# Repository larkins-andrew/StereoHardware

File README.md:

# StereoBoy Hardware
# KiCad hardware files for Original GameBoy Color cartridge, GameBoy Pocket logic board, and StereoBoy logic board

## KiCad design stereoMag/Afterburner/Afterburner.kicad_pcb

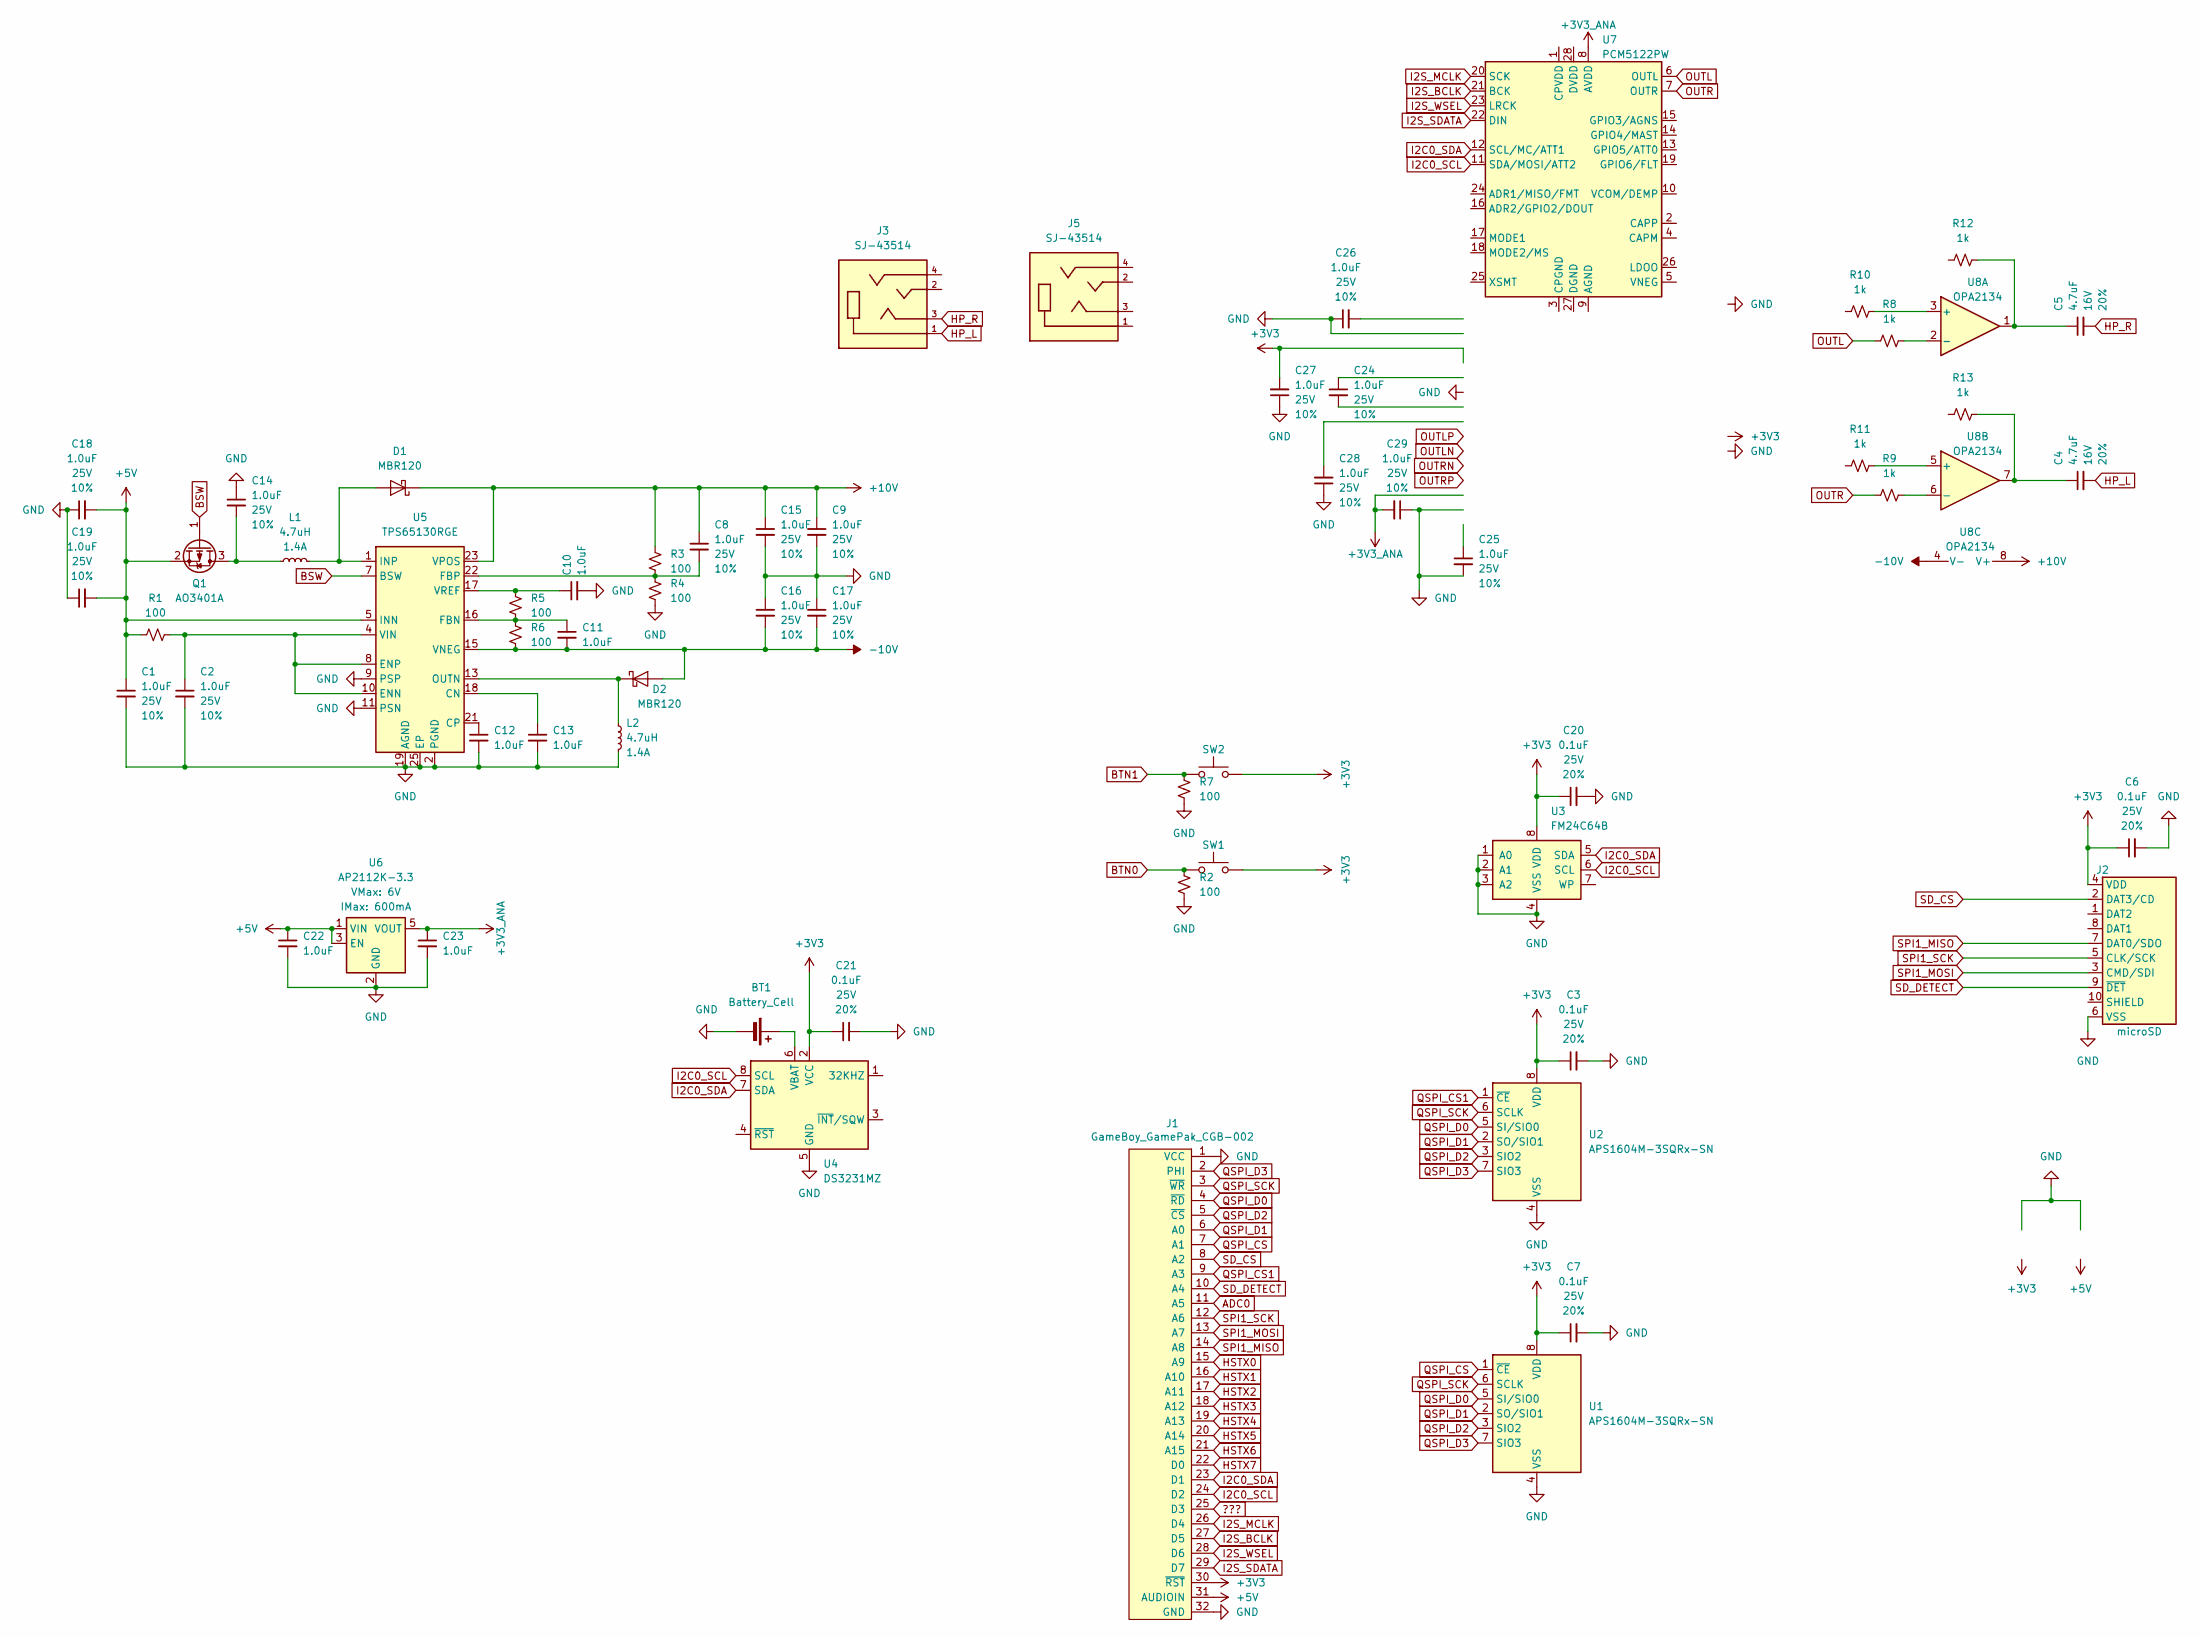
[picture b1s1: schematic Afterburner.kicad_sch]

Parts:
BT1: Battery_Cell; BatteryHolder_Keystone_3001_1x12mm
C1, C2, C10, C12, C13, C22, C23: 1.0uF; C_0603_1608Metric; Voltage 25V; Tolerance 10%
C3, C7, C20, C21: 0.1uF; C_0805_2012Metric; Voltage 25V; Tolerance 20%
C4, C5: 4.7uF; C_1206_3216Metric; Voltage 16V; Tolerance 20%
C6: 0.1uF; C_0603_1608Metric; Voltage 25V; Tolerance 20%
C8, C9, C11, C15, C16, C17, C18, C19: 1.0uF; C_1206_3216Metric; Voltage 25V; Tolerance 10%
C14, C28: 1.0uF; C_0805_2012Metric; Voltage 25V; Tolerance 10%
C24, C25, C26, C27, C29: 1.0uF; C_0402_1005Metric; Voltage 25V; Tolerance 10%
D1, D2: MBR120; D_SOD-123F
J1: GameBoy_GamePak_CGB-002; GameBoy_GamePak_CGB-002_P1.50mm_Edge
J2: microSD; microSD_External_Pin
J3, J5: SJ-43514; SJ_43514; PART_REV 1.04
L1, L2: 4.7uH; L_APV_ANR4012
Q1: AO3401A; SOT-23
R1, R2, R3, R4, R5, R6, R7: 100; R_0603_1608Metric
R8, R9, R10, R11, R12, R13: 1k; R_0603_1608Metric
SW1, SW2: PTH_RA_7.4x4.3mm; Push_PTH_RA_7.4x4.3mm
U1, U2: APS1604M-3SQRx-SN; SOIC-8_3.9x4.9mm_P1.27mm
U3: FM24C64B; SOIC-8_3.9x4.9mm_P1.27mm
U4: DS3231MZ; SOIC-8_3.9x4.9mm_P1.27mm
U5: TPS65130RGE; VQFN-24-1EP_4x4mm_P0.5mm_EP2.45x2.45mm_ThermalVias
U6: AP2112K-3.3; SOT23-5
U7: PCM5122PW; TSSOP-28_4.4x9.7mm_P0.65mm
U8: OPA2134

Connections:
+3V3: C3.1, C6.1, C7.1, C20.1, C21.1, C27.2, J1.30 (~RST), J2.4 (VDD), SW1.2, SW2.2, U1.8 (VDD), U2.8 (VDD), U3.8 (VDD), U4.2 (VCC)
+3V3_ANA: C23.1, C29.2, U6.5 (VOUT), U7.8 (AVDD)
+5V: C1.1, C18.2, C19.2, C22.1, J1.31 (AUDIOIN), Q1.2 (S), R1.1, U5.5 (INN), U5.6 (INN), U6.1 (VIN), U6.3 (EN)
+10V: C8.1, C9.1, C15.1, D1.1 (K), R3.2, U5.23 (VPOS), U8.8 (V+)
-10V: C11.2, C16.2, C17.2, D2.2 (A), R6.1, U5.15 (VNEG), U8.4 (V-)
???: J1.25 (D3)
ADC0: J1.11 (A5)
BSW: Q1.1 (G), U5.7 (BSW)
BTN0: R2.2, SW1.1
BTN1: R7.2, SW2.1
GND: BT1.2 (-), C1.2, C2.2, C3.2, C6.2, C7.2, C9.2, C10.2, C12.2, C13.2, C14.1, C15.2, C16.1, C17.1, C18.1, C19.1, C20.2, C21.2, C22.2, C23.2, C25.2, C26.1, C27.1, C28.1, C29.1, J1.1 (VCC), J1.32 (GND), J2.6 (VSS), L2.2, R2.1, R4.1, R7.1, U1.4 (VSS), U2.4 (VSS), U3.1 (A0), U3.2 (A1), U3.3 (A2), U3.4 (VSS), U4.5 (GND), U5.2 (PGND), U5.3 (PGND), U5.9 (PSP), U5.11 (PSN), U5.19 (AGND), U5.25 (EP), U6.2 (GND)
HP_L: C4.2, J3.1
HP_R: C5.2, J3.3
HSTX0: J1.15 (A9)
HSTX1: J1.16 (A10)
HSTX2: J1.17 (A11)
HSTX3: J1.18 (A12)
HSTX4: J1.19 (A13)
HSTX5: J1.20 (A14)
HSTX6: J1.21 (A15)
HSTX7: J1.22 (D0)
I2C0_SCL: J1.24 (D2), U3.6 (SCL), U4.8 (SCL), U7.11 (SDA/MOSI/ATT2)
I2C0_SDA: J1.23 (D1), U3.5 (SDA), U4.7 (SDA), U7.12 (SCL/MC/ATT1)
I2S_BCLK: J1.27 (D5), U7.21 (BCK)
I2S_MCLK: J1.26 (D4), U7.20 (SCK)
I2S_SDATA: J1.29 (D7), U7.22 (DIN)
I2S_WSEL: J1.28 (D6), U7.23 (LRCK)
unnamed: BT1.1 (+), U4.6 (VBAT)
unnamed: C4.1, R13.2, U8.7
unnamed: C5.1, R12.2, U8.1
unnamed: D1.2 (A), L1.2, U5.1 (INP), U5.24 (INP)
unnamed: D2.1 (K), L2.1, U5.13 (OUTN), U5.14 (OUTN)
unnamed: C14.2, L1.1, Q1.3 (D)
unnamed: C13.1, U5.18 (CN)
unnamed: C12.1, U5.21 (CP)
unnamed: C2.1, R1.2, U5.4 (VIN), U5.8 (ENP), U5.10 (ENN)
unnamed: C11.1, R5.1, R6.2, U5.16 (FBN)
unnamed: C8.2, R3.1, R4.2, U5.22 (FBP)
unnamed: C10.1, R5.2, U5.17 (VREF)
unnamed: R10.2, U8.3 (+)
unnamed: R8.2, U8.2 (-)
unnamed: R11.2, U8.5 (+)
unnamed: R9.2, U8.6 (-)
OUTL: R8.1, U7.6 (OUTL)
OUTR: R9.1, U7.7 (OUTR)
QSPI_CS: J1.7 (A1), U1.1 (~CE)
QSPI_CS1: J1.9 (A3), U2.1 (~CE)
QSPI_D0: J1.4 (~RD), U1.5 (SI/SIO0), U2.5 (SI/SIO0)
QSPI_D1: J1.6 (A0), U1.2 (SO/SIO1), U2.2 (SO/SIO1)
QSPI_D2: J1.5 (~CS), U1.3 (SIO2), U2.3 (SIO2)
QSPI_D3: J1.2 (PHI), U1.7 (SIO3), U2.7 (SIO3)
QSPI_SCK: J1.3 (~WR), U1.6 (SCLK), U2.6 (SCLK)
SD_CS: J1.8 (A2), J2.2 (DAT3/CD)
SD_DETECT: J1.10 (A4), J2.9 (~DET)
SPI1_MISO: J1.14 (A8), J2.7 (DAT0/SDO)
SPI1_MOSI: J1.13 (A7), J2.3 (CMD/SDI)
SPI1_SCK: J1.12 (A6), J2.5 (CLK/SCK)

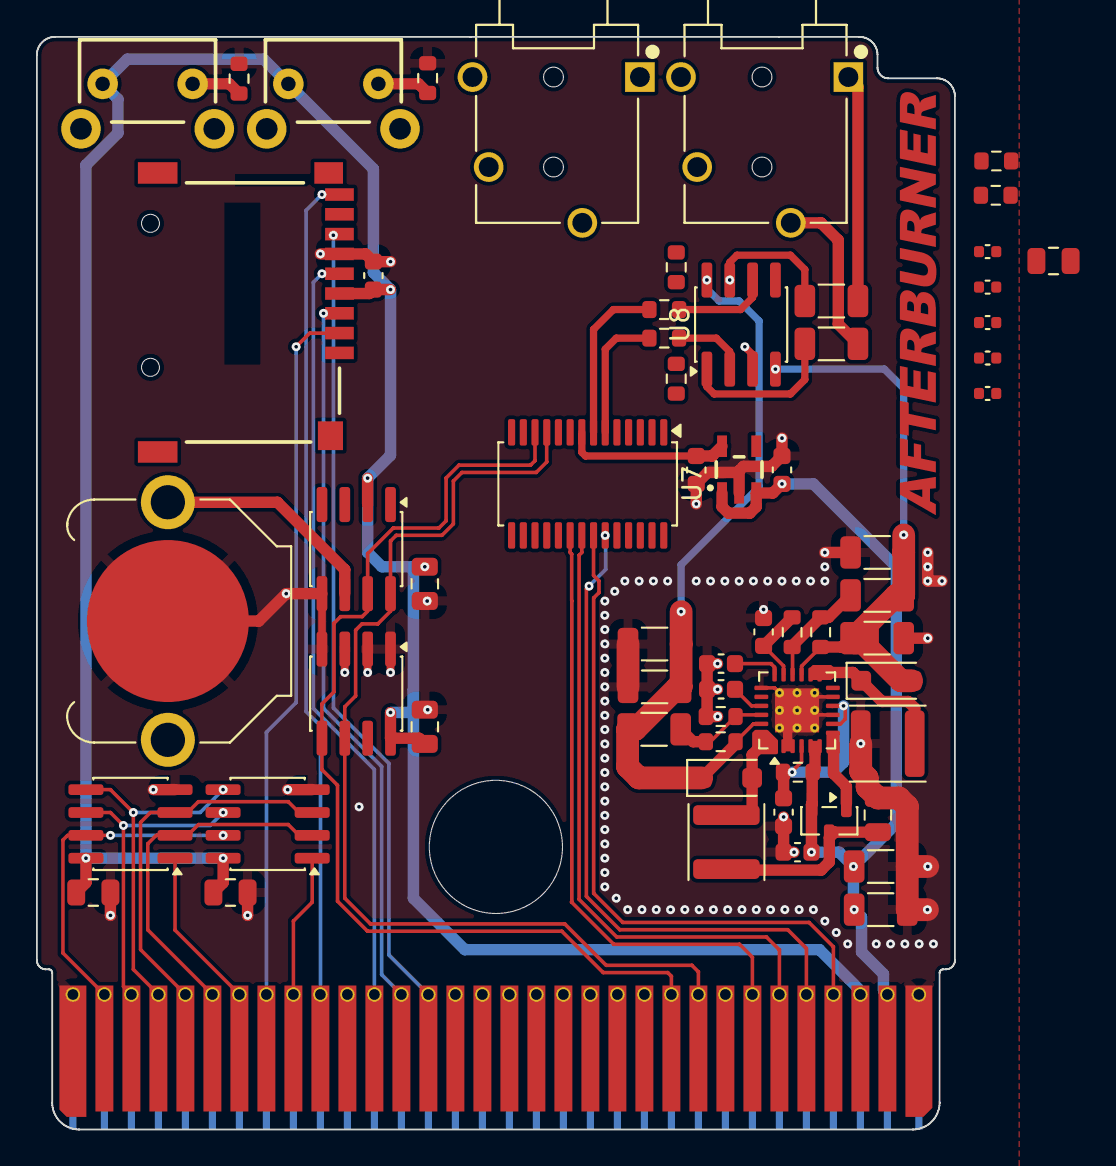
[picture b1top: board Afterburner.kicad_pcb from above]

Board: 2 copper layers, 51.0 x 60.7 mm, 62 parts (0 on the bottom side), 47 nets.

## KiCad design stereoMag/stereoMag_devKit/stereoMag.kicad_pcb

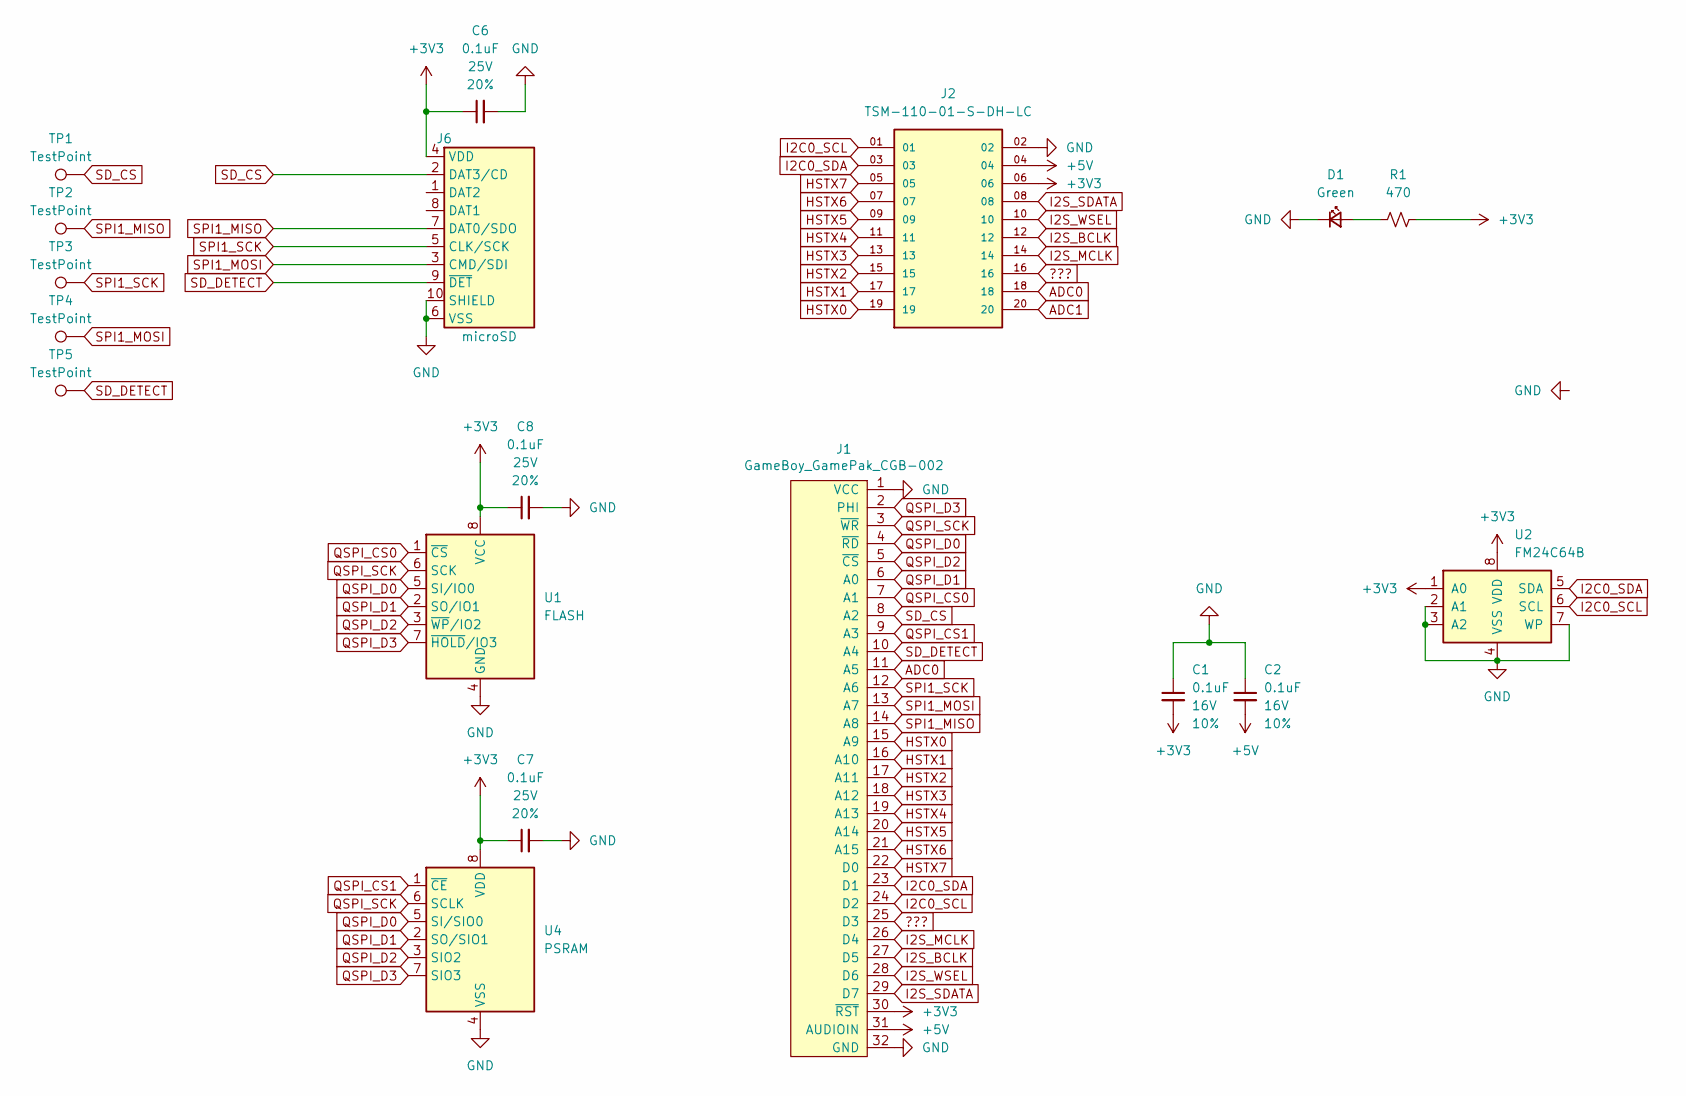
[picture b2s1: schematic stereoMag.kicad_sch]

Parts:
C1, C2: 0.1uF; C_1206_3216Metric; Voltage 16V; Tolerance 10%
C6, C7, C8: 0.1uF; C_0603_1608Metric; Voltage 25V; Tolerance 20%
D1: Green; LED_0603_1608Metric_Green
J1: GameBoy_GamePak_CGB-002; GameBoy_GamePak_CGB-002_P1.50mm_Edge
J2: TSM-110-01-S-DH-LC; SAMTEC_TSM-110-01-S-DH-LC; PARTREV R
J6: microSD; microSD_External_Pin
R1: 470; R_0603_1608Metric
TP1, TP2, TP3, TP4, TP5: TestPoint; TestPoint_Pad_D1.0mm
U1: FLASH; SOIC-8_3.9x4.9mm_P1.27mm
U2: FM24C64B; SOIC-8_3.9x4.9mm_P1.27mm
U4: PSRAM; SOIC-8_3.9x4.9mm_P1.27mm

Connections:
+3V3: C1.2, C6.1, C7.1, C8.1, J1.30 (~RST), J2.06, J6.4 (VDD), R1.2, U1.8 (VCC), U2.1 (A0), U2.8 (VDD), U4.8 (VDD)
+5V: C2.2, J1.31 (AUDIOIN), J2.04
???: J1.25 (D3), J2.16
ADC0: J1.11 (A5), J2.18
ADC1: J2.20
GND: C1.1, C2.1, C6.2, C7.2, C8.2, D1.1 (K), J1.1 (VCC), J1.32 (GND), J2.02, J6.6 (VSS), J6.10 (SHIELD), U1.4 (GND), U2.2 (A1), U2.3 (A2), U2.4 (VSS), U2.7 (WP), U4.4 (VSS)
HSTX0: J1.15 (A9), J2.19
HSTX1: J1.16 (A10), J2.17
HSTX2: J1.17 (A11), J2.15
HSTX3: J1.18 (A12), J2.13
HSTX4: J1.19 (A13), J2.11
HSTX5: J1.20 (A14), J2.09
HSTX6: J1.21 (A15), J2.07
HSTX7: J1.22 (D0), J2.05
I2C0_SCL: J1.24 (D2), J2.01, U2.6 (SCL)
I2C0_SDA: J1.23 (D1), J2.03, U2.5 (SDA)
I2S_BCLK: J1.27 (D5), J2.12
I2S_MCLK: J1.26 (D4), J2.14
I2S_SDATA: J1.29 (D7), J2.08
I2S_WSEL: J1.28 (D6), J2.10
unnamed: D1.2 (A), R1.1
QSPI_CS0: J1.7 (A1), U1.1 (~CS)
QSPI_CS1: J1.9 (A3), U4.1 (~CE)
QSPI_D0: J1.4 (~RD), U1.5 (SI/IO0), U4.5 (SI/SIO0)
QSPI_D1: J1.6 (A0), U1.2 (SO/IO1), U4.2 (SO/SIO1)
QSPI_D2: J1.5 (~CS), U1.3 (~WP/IO2), U4.3 (SIO2)
QSPI_D3: J1.2 (PHI), U1.7 (~HOLD/IO3), U4.7 (SIO3)
QSPI_SCK: J1.3 (~WR), U1.6 (SCK), U4.6 (SCLK)
SD_CS: J1.8 (A2), J6.2 (DAT3/CD), TP1.1
SD_DETECT: J1.10 (A4), J6.9 (~DET), TP5.1
SPI1_MISO: J1.14 (A8), J6.7 (DAT0/SDO), TP2.1
SPI1_MOSI: J1.13 (A7), J6.3 (CMD/SDI), TP4.1
SPI1_SCK: J1.12 (A6), J6.5 (CLK/SCK), TP3.1

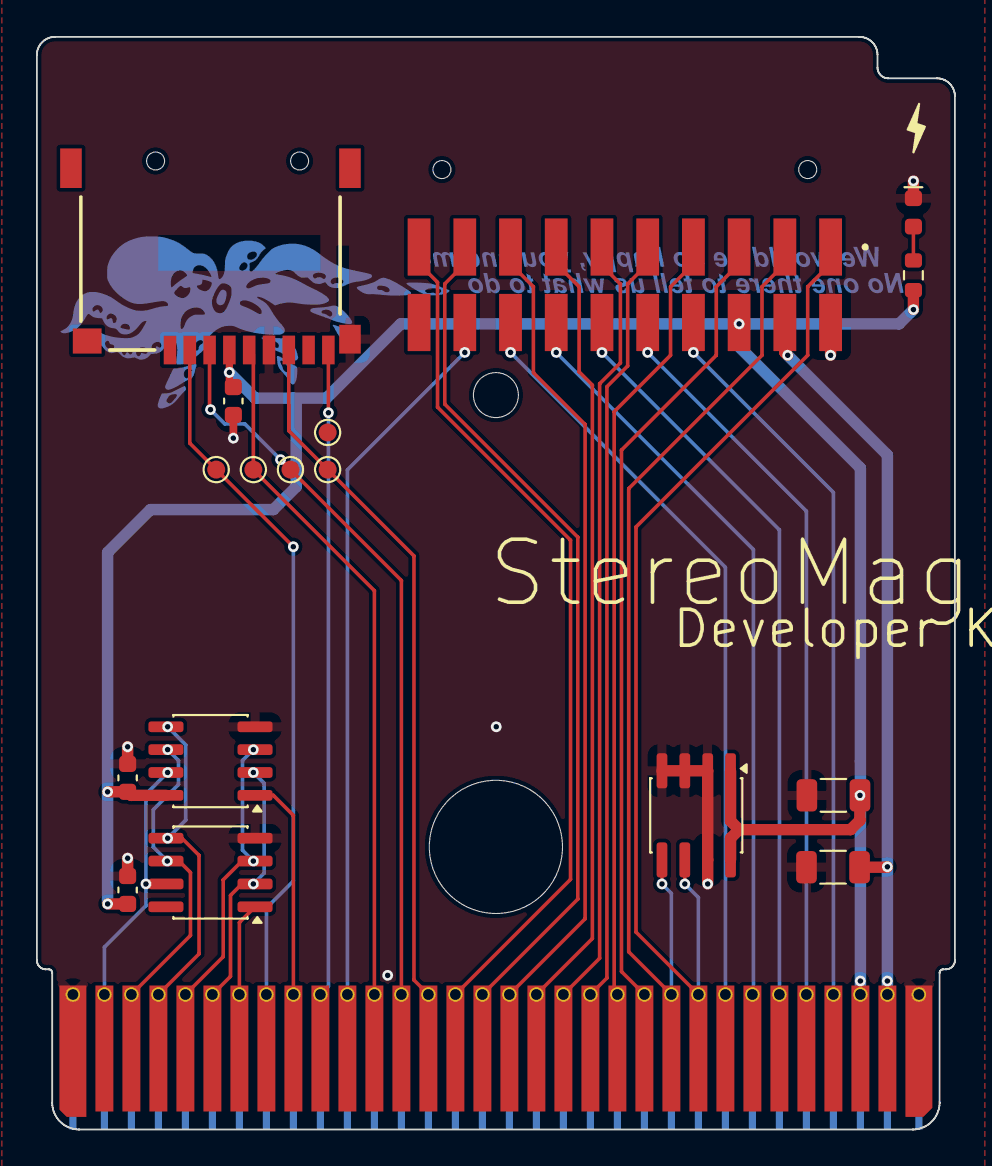
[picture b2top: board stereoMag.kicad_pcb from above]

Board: 2 copper layers, 51.0 x 60.7 mm, 18 parts (0 on the bottom side), 32 nets.

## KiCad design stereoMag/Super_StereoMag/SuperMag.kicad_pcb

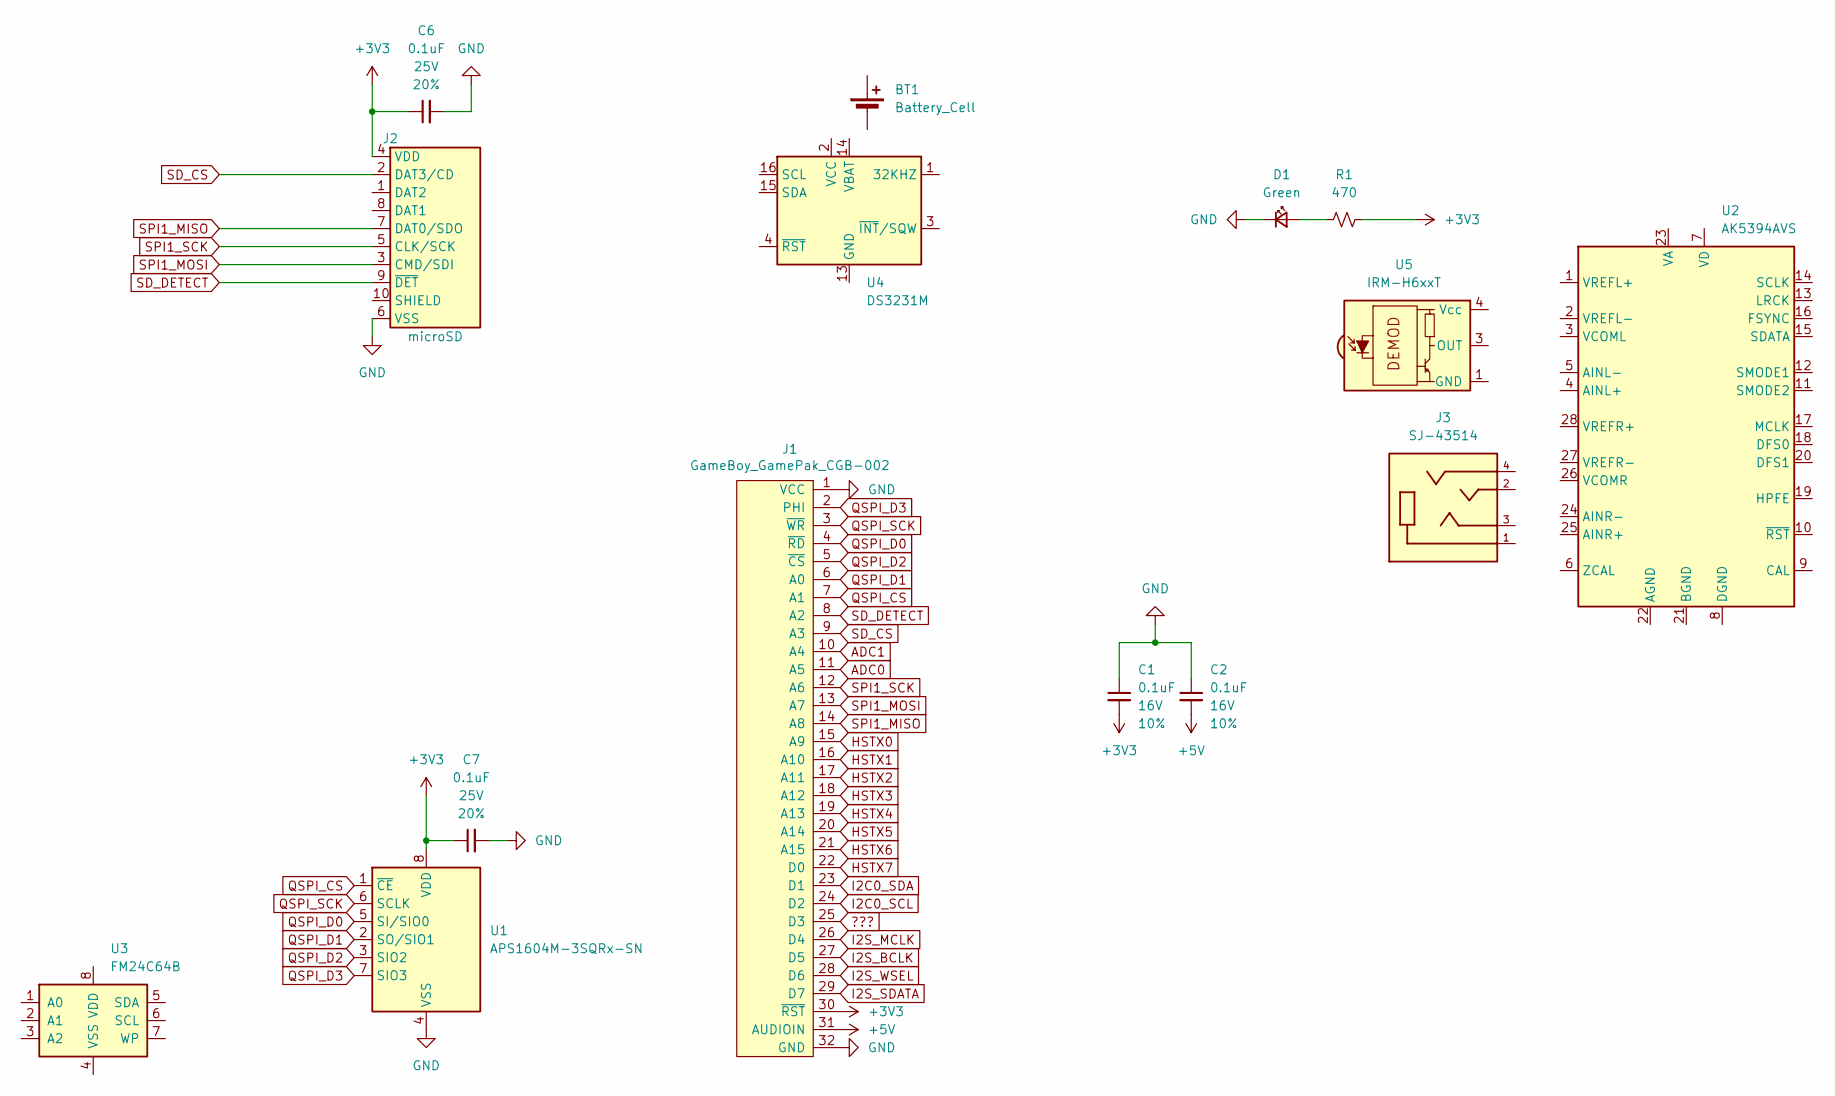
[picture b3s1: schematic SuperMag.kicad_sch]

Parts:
BT1: Battery_Cell; BatteryHolder_Keystone_3001_1x12mm
C1, C2: 0.1uF; CP_Elec_5x3; Voltage 16V; Tolerance 10%
C6, C7: 0.1uF; C_0603_1608Metric; Voltage 25V; Tolerance 20%
D1: Green; LED_0603_1608Metric_Green
J1: GameBoy_GamePak_CGB-002; GameBoy_GamePak_CGB-002_P1.50mm_Edge
J2: microSD; microSD_External_Pin
J3: SJ-43514; SJ_43514; PART_REV 1.04
R1: 470; R_0603_1608Metric
U1: APS1604M-3SQRx-SN; SOIC-8_3.9x4.9mm_P1.27mm
U2: AK5394AVS; SOIC-28W_7.5x18.7mm_P1.27mm
U3: FM24C64B; SOIC-8_3.9x4.9mm_P1.27mm
U4: DS3231M; SOIC-16W_7.5x10.3mm_P1.27mm
U5: IRM-H6xxT; Everlight_IRM-H6xxT

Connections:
+3V3: C1.2, C6.1, C7.1, J1.30 (~RST), J2.4 (VDD), R1.2, U1.8 (VDD)
+5V: C2.2, J1.31 (AUDIOIN)
???: J1.25 (D3)
ADC0: J1.11 (A5)
ADC1: J1.10 (A4)
GND: C1.1, C2.1, C6.2, C7.2, D1.1 (K), J1.1 (VCC), J1.32 (GND), J2.6 (VSS), U1.4 (VSS)
HSTX0: J1.15 (A9)
HSTX1: J1.16 (A10)
HSTX2: J1.17 (A11)
HSTX3: J1.18 (A12)
HSTX4: J1.19 (A13)
HSTX5: J1.20 (A14)
HSTX6: J1.21 (A15)
HSTX7: J1.22 (D0)
I2C0_SCL: J1.24 (D2)
I2C0_SDA: J1.23 (D1)
I2S_BCLK: J1.27 (D5)
I2S_MCLK: J1.26 (D4)
I2S_SDATA: J1.29 (D7)
I2S_WSEL: J1.28 (D6)
unnamed: D1.2 (A), R1.1
unnamed: U4.5 (GND), U4.6 (GND), U4.7 (GND), U4.8 (GND), U4.9 (GND), U4.10 (GND), U4.11 (GND), U4.12 (GND), U4.13 (GND)
unnamed: U5.1 (GND), U5.2 (GND)
QSPI_CS: J1.7 (A1), U1.1 (~CE)
QSPI_D0: J1.4 (~RD), U1.5 (SI/SIO0)
QSPI_D1: J1.6 (A0), U1.2 (SO/SIO1)
QSPI_D2: J1.5 (~CS), U1.3 (SIO2)
QSPI_D3: J1.2 (PHI), U1.7 (SIO3)
QSPI_SCK: J1.3 (~WR), U1.6 (SCLK)
SD_CS: J1.9 (A3), J2.2 (DAT3/CD)
SD_DETECT: J1.8 (A2), J2.9 (~DET)
SPI1_MISO: J1.14 (A8), J2.7 (DAT0/SDO)
SPI1_MOSI: J1.13 (A7), J2.3 (CMD/SDI)
SPI1_SCK: J1.12 (A6), J2.5 (CLK/SCK)

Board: 2 copper layers, 15 parts (0 on the bottom side), 17 nets, no tracks yet.
